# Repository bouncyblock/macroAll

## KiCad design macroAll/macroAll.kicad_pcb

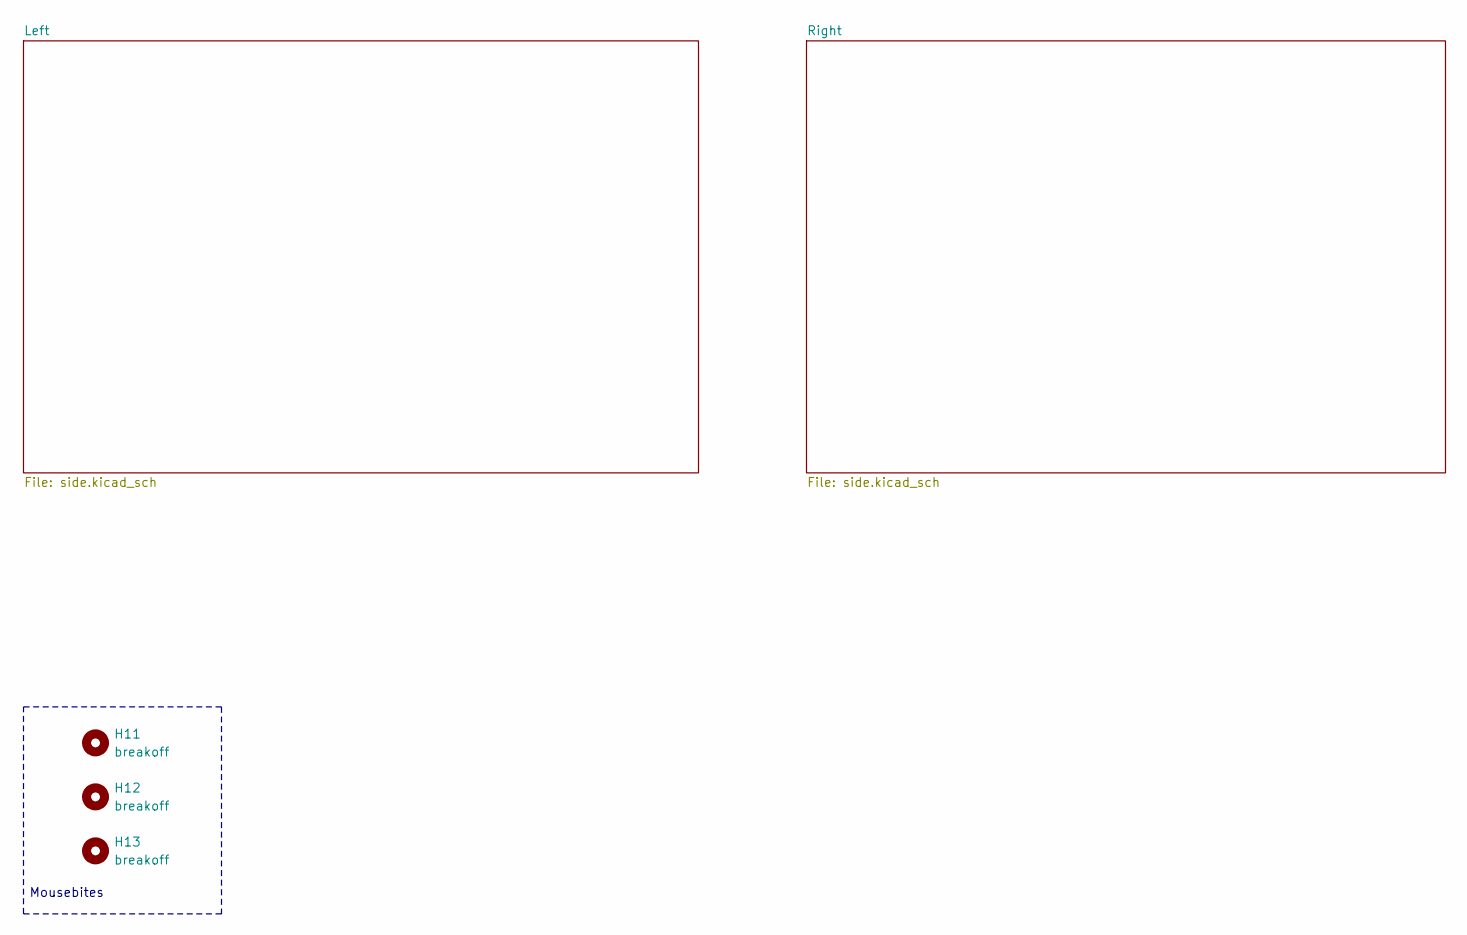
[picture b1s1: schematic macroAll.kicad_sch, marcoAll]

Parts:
H11, H12, H13: breakoff; mouse-bite-5mm-slot

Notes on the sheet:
Mousebites

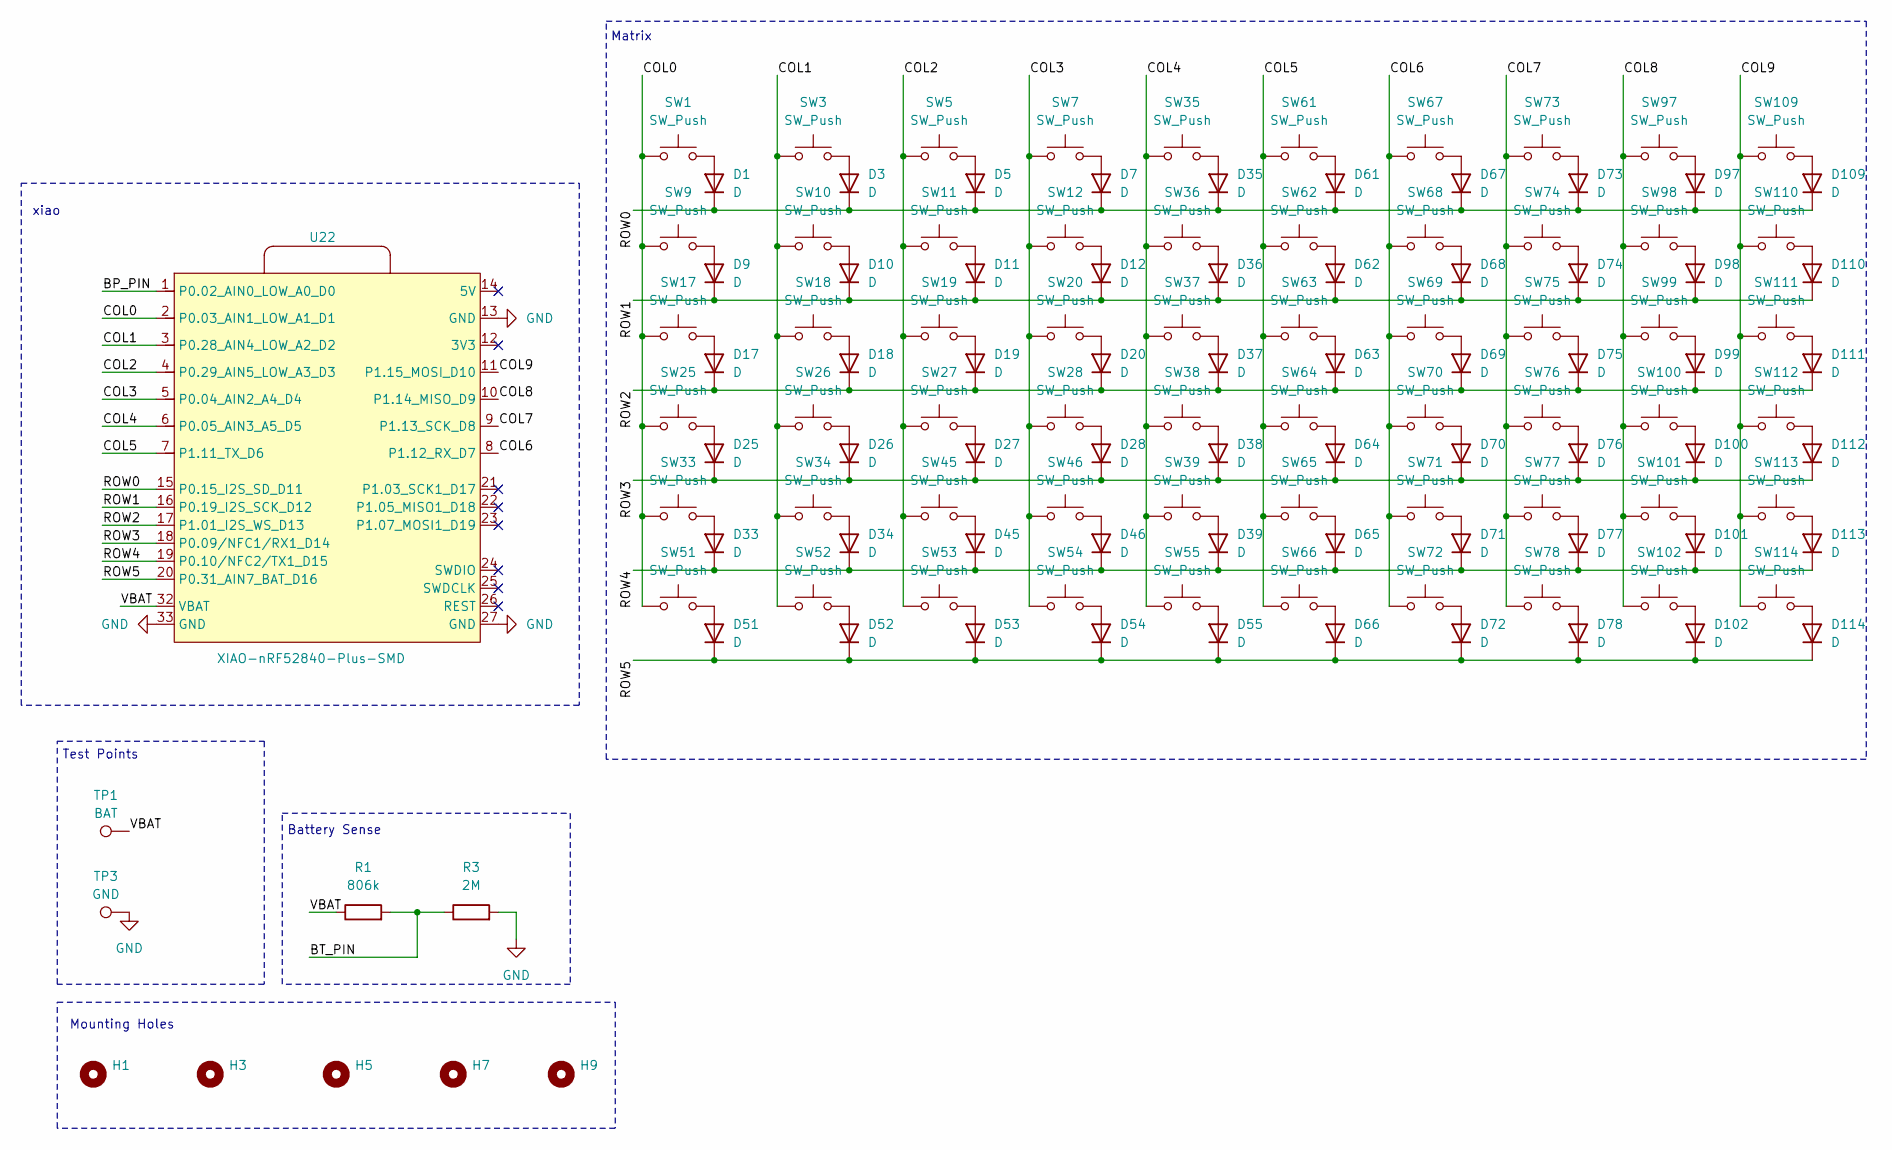
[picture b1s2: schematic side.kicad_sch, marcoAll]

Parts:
D1, D3, D5, D7, D9, D10, D11, D12, D17, D18, D19, D20, D25, D26, D27, D28, D33, D34, D35, D36, D37, D38, D39, D45, D46, D51, D52, D53, D54, D55, D61, D62, D63, D64, D65, D66, D67, D68, D69, D70, D71, D72, D73, D74, D75, D76, D77, D78, D97, D98, D99, D100, D101, D102, D109, D110, D111, D112, D113, D114: D; D_SOD-123
H1, H3, H5, H7, H9: MountingHole; MountingHole_2.5mm
R1: 806k; R_0805_2012Metric
R3: 2M; R_0805_2012Metric
SW1, SW3, SW5, SW7, SW9, SW10, SW11, SW12, SW17, SW18, SW19, SW20, SW25, SW26, SW27, SW28, SW33, SW34, SW35, SW36, SW37, SW38, SW39, SW45, SW46, SW51, SW52, SW53, SW54, SW55, SW61, SW62, SW63, SW64, SW65, SW66, SW67, SW68, SW69, SW70, SW71, SW72, SW73, SW74, SW75, SW76, SW77, SW78, SW97, SW98, SW99, SW100, SW101, SW102, SW109, SW110, SW111, SW112, SW113, SW114: SW_Push; SW_Hotswap_Kailh_Choc_V1
TP1: BAT; TestPoint_Pad_D2.0mm
TP3: GND; TestPoint_Pad_D2.0mm
U22: XIAO-nRF52840-Plus-SMD

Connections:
/Left/BP_PIN: U22.1 (P0.02_AIN0_LOW_A0_D0)
/Left/BT_PIN: R1.2, R3.1
/Left/COL0: SW1.1, SW9.1, SW17.1, SW25.1, SW33.1, SW51.1, U22.2 (P0.03_AIN1_LOW_A1_D1)
/Left/COL1: SW3.1, SW10.1, SW18.1, SW26.1, SW34.1, SW52.1, U22.3 (P0.28_AIN4_LOW_A2_D2)
/Left/COL2: SW5.1, SW11.1, SW19.1, SW27.1, SW45.1, SW53.1, U22.4 (P0.29_AIN5_LOW_A3_D3)
/Left/COL3: SW7.1, SW12.1, SW20.1, SW28.1, SW46.1, SW54.1, U22.5 (P0.04_AIN2_A4_D4)
/Left/COL4: SW35.1, SW36.1, SW37.1, SW38.1, SW39.1, SW55.1, U22.6 (P0.05_AIN3_A5_D5)
/Left/COL5: SW61.1, SW62.1, SW63.1, SW64.1, SW65.1, SW66.1, U22.7 (P1.11_TX_D6)
/Left/COL6: SW67.1, SW68.1, SW69.1, SW70.1, SW71.1, SW72.1, U22.8 (P1.12_RX_D7)
/Left/COL7: SW73.1, SW74.1, SW75.1, SW76.1, SW77.1, SW78.1, U22.9 (P1.13_SCK_D8)
/Left/COL8: SW97.1, SW98.1, SW99.1, SW100.1, SW101.1, SW102.1, U22.10 (P1.14_MISO_D9)
/Left/ROW0: D1.1 (K), D3.1 (K), D5.1 (K), D7.1 (K), D35.1 (K), D61.1 (K), D67.1 (K), D73.1 (K), D97.1 (K), D109.1 (K), U22.15 (P0.15_I2S_SD_D11)
/Left/ROW1: D9.1 (K), D10.1 (K), D11.1 (K), D12.1 (K), D36.1 (K), D62.1 (K), D68.1 (K), D74.1 (K), D98.1 (K), D110.1 (K), U22.16 (P0.19_I2S_SCK_D12)
/Left/ROW2: D17.1 (K), D18.1 (K), D19.1 (K), D20.1 (K), D37.1 (K), D63.1 (K), D69.1 (K), D75.1 (K), D99.1 (K), D111.1 (K), U22.17 (P1.01_I2S_WS_D13)
/Left/ROW4: D33.1 (K), D34.1 (K), D39.1 (K), D45.1 (K), D46.1 (K), D65.1 (K), D71.1 (K), D77.1 (K), D101.1 (K), D113.1 (K), U22.19 (P0.10/NFC2/TX1_D15)
/Left/VBAT: R1.1, TP1.1, U22.32 (VBAT)
GND: R3.2, TP3.1, U22.13 (GND), U22.27 (GND), U22.33 (GND); also elsewhere on the board
unnamed: D1.2 (A), SW1.2
unnamed: D3.2 (A), SW3.2
unnamed: D5.2 (A), SW5.2
unnamed: D7.2 (A), SW7.2
unnamed: D9.2 (A), SW9.2
unnamed: D10.2 (A), SW10.2
unnamed: D11.2 (A), SW11.2
unnamed: D12.2 (A), SW12.2
unnamed: D17.2 (A), SW17.2
unnamed: D18.2 (A), SW18.2
unnamed: D19.2 (A), SW19.2
unnamed: D20.2 (A), SW20.2
unnamed: D25.2 (A), SW25.2
unnamed: D26.2 (A), SW26.2
unnamed: D27.2 (A), SW27.2
unnamed: D28.2 (A), SW28.2
unnamed: D33.2 (A), SW33.2
unnamed: D34.2 (A), SW34.2
unnamed: D35.2 (A), SW35.2
unnamed: D36.2 (A), SW36.2
unnamed: D37.2 (A), SW37.2
unnamed: D38.2 (A), SW38.2
unnamed: D39.2 (A), SW39.2
unnamed: D45.2 (A), SW45.2
unnamed: D46.2 (A), SW46.2
unnamed: D51.2 (A), SW51.2
unnamed: D52.2 (A), SW52.2
unnamed: D53.2 (A), SW53.2
unnamed: D54.2 (A), SW54.2
unnamed: D55.2 (A), SW55.2
unnamed: D61.2 (A), SW61.2
unnamed: D62.2 (A), SW62.2
unnamed: D63.2 (A), SW63.2
unnamed: D64.2 (A), SW64.2
unnamed: D65.2 (A), SW65.2
unnamed: D66.2 (A), SW66.2
unnamed: D67.2 (A), SW67.2
unnamed: D68.2 (A), SW68.2
unnamed: D69.2 (A), SW69.2
unnamed: D70.2 (A), SW70.2
unnamed: D71.2 (A), SW71.2
unnamed: D72.2 (A), SW72.2
unnamed: D73.2 (A), SW73.2
unnamed: D74.2 (A), SW74.2
unnamed: D75.2 (A), SW75.2
unnamed: D76.2 (A), SW76.2
unnamed: D77.2 (A), SW77.2
unnamed: D78.2 (A), SW78.2
unnamed: D97.2 (A), SW97.2
unnamed: D98.2 (A), SW98.2
unnamed: D99.2 (A), SW99.2
unnamed: D100.2 (A), SW100.2
unnamed: D101.2 (A), SW101.2
unnamed: D102.2 (A), SW102.2
unnamed: D109.2 (A), SW109.2
unnamed: D110.2 (A), SW110.2
unnamed: D111.2 (A), SW111.2
unnamed: D113.2 (A), SW113.2

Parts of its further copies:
D2, D4, D6, D8, D13, D14, D15, D16, D21, D22, D23, D24, D29, D30, D31, D32, D40, D41, D42, D43, D44, D47, D48, D49, D50, D56, D57, D58, D59, D60, D79, D80, D81, D82, D83, D84, D85, D86, D87, D88, D89, D90, D91, D92, D93, D94, D95, D96, D103, D104, D105, D106, D107, D108, D115, D116, D117, D118, D119, D120: D; D_SOD-123
H2, H4, H6, H8, H10: MountingHole; MountingHole_2.5mm
R2: 806k; R_0805_2012Metric
R4: 2M; R_0805_2012Metric
SW2, SW4, SW6, SW8, SW13, SW14, SW15, SW16, SW21, SW22, SW23, SW24, SW29, SW30, SW31, SW32, SW40, SW41, SW42, SW43, SW44, SW47, SW48, SW49, SW50, SW56, SW57, SW58, SW59, SW60, SW79, SW80, SW81, SW82, SW83, SW84, SW85, SW86, SW87, SW88, SW89, SW90, SW91, SW92, SW93, SW94, SW95, SW96, SW103, SW104, SW105, SW106, SW107, SW108, SW115, SW116, SW117, SW118, SW119, SW120: SW_Push; SW_Hotswap_Kailh_Choc_V1
TP2: BAT; TestPoint_Pad_D2.0mm
TP4: GND; TestPoint_Pad_D2.0mm
U23: XIAO-nRF52840-Plus-SMD

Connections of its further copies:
/Right/BP_PIN: U23.1 (P0.02_AIN0_LOW_A0_D0)
/Right/BT_PIN: R2.2, R4.1
/Right/COL0: SW2.1, SW13.1, SW21.1, SW29.1, SW47.1, SW56.1, U23.2 (P0.03_AIN1_LOW_A1_D1)
/Right/COL1: SW4.1, SW14.1, SW22.1, SW30.1, SW48.1, SW57.1, U23.3 (P0.28_AIN4_LOW_A2_D2)
/Right/COL2: SW6.1, SW15.1, SW23.1, SW31.1, SW49.1, SW58.1, U23.4 (P0.29_AIN5_LOW_A3_D3)
/Right/COL3: SW8.1, SW16.1, SW24.1, SW32.1, SW50.1, SW59.1, U23.5 (P0.04_AIN2_A4_D4)
/Right/COL4: SW40.1, SW41.1, SW42.1, SW43.1, SW44.1, SW60.1, U23.6 (P0.05_AIN3_A5_D5)
/Right/COL5: SW79.1, SW80.1, SW81.1, SW82.1, SW83.1, SW84.1, U23.7 (P1.11_TX_D6)
/Right/COL6: SW85.1, SW86.1, SW87.1, SW88.1, SW89.1, SW90.1, U23.8 (P1.12_RX_D7)
/Right/COL7: SW91.1, SW92.1, SW93.1, SW94.1, SW95.1, SW96.1, U23.9 (P1.13_SCK_D8)
/Right/COL8: SW103.1, SW104.1, SW105.1, SW106.1, SW107.1, SW108.1, U23.10 (P1.14_MISO_D9)
/Right/ROW0: D2.1 (K), D4.1 (K), D6.1 (K), D8.1 (K), D40.1 (K), D79.1 (K), D85.1 (K), D91.1 (K), D103.1 (K), D115.1 (K), U23.15 (P0.15_I2S_SD_D11)
/Right/ROW1: D13.1 (K), D14.1 (K), D15.1 (K), D16.1 (K), D41.1 (K), D80.1 (K), D86.1 (K), D92.1 (K), D104.1 (K), D116.1 (K), U23.16 (P0.19_I2S_SCK_D12)
/Right/ROW2: D21.1 (K), D22.1 (K), D23.1 (K), D24.1 (K), D42.1 (K), D81.1 (K), D87.1 (K), D93.1 (K), D105.1 (K), D117.1 (K), U23.17 (P1.01_I2S_WS_D13)
/Right/ROW4: D44.1 (K), D47.1 (K), D48.1 (K), D49.1 (K), D50.1 (K), D83.1 (K), D89.1 (K), D95.1 (K), D107.1 (K), D119.1 (K), U23.19 (P0.10/NFC2/TX1_D15)
/Right/VBAT: R2.1, TP2.1, U23.32 (VBAT)
GND: R4.2, TP4.1, U23.13 (GND), U23.27 (GND), U23.33 (GND); also elsewhere on the board
unnamed: D2.2 (A), SW2.2
unnamed: D4.2 (A), SW4.2
unnamed: D6.2 (A), SW6.2
unnamed: D8.2 (A), SW8.2
unnamed: D13.2 (A), SW13.2
unnamed: D14.2 (A), SW14.2
unnamed: D15.2 (A), SW15.2
unnamed: D16.2 (A), SW16.2
unnamed: D21.2 (A), SW21.2
unnamed: D22.2 (A), SW22.2
unnamed: D23.2 (A), SW23.2
unnamed: D24.2 (A), SW24.2
unnamed: D29.2 (A), SW29.2
unnamed: D30.2 (A), SW30.2
unnamed: D31.2 (A), SW31.2
unnamed: D32.2 (A), SW32.2
unnamed: D40.2 (A), SW40.2
unnamed: D41.2 (A), SW41.2
unnamed: D42.2 (A), SW42.2
unnamed: D43.2 (A), SW43.2
unnamed: D44.2 (A), SW44.2
unnamed: D47.2 (A), SW47.2
unnamed: D48.2 (A), SW48.2
unnamed: D49.2 (A), SW49.2
unnamed: D50.2 (A), SW50.2
unnamed: D56.2 (A), SW56.2
unnamed: D57.2 (A), SW57.2
unnamed: D58.2 (A), SW58.2
unnamed: D59.2 (A), SW59.2
unnamed: D60.2 (A), SW60.2
unnamed: D79.2 (A), SW79.2
unnamed: D80.2 (A), SW80.2
unnamed: D81.2 (A), SW81.2
unnamed: D82.2 (A), SW82.2
unnamed: D83.2 (A), SW83.2
unnamed: D84.2 (A), SW84.2
unnamed: D85.2 (A), SW85.2
unnamed: D86.2 (A), SW86.2
unnamed: D87.2 (A), SW87.2
unnamed: D88.2 (A), SW88.2
unnamed: D89.2 (A), SW89.2
unnamed: D90.2 (A), SW90.2
unnamed: D91.2 (A), SW91.2
unnamed: D92.2 (A), SW92.2
unnamed: D93.2 (A), SW93.2
unnamed: D94.2 (A), SW94.2
unnamed: D95.2 (A), SW95.2
unnamed: D96.2 (A), SW96.2
unnamed: D103.2 (A), SW103.2
unnamed: D104.2 (A), SW104.2
unnamed: D105.2 (A), SW105.2
unnamed: D106.2 (A), SW106.2
unnamed: D107.2 (A), SW107.2
unnamed: D108.2 (A), SW108.2
unnamed: D115.2 (A), SW115.2
unnamed: D116.2 (A), SW116.2
unnamed: D117.2 (A), SW117.2
unnamed: D118.2 (A), SW118.2
unnamed: D119.2 (A), SW119.2
unnamed: D120.2 (A), SW120.2

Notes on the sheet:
Matrix
xiao
Mounting Holes
Battery Sense
Test Points

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
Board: 2 copper layers, 259 parts (0 on the bottom side), 155 nets, no tracks yet.

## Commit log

2025-10-29 added readme
2025-10-30 added OPL libraries and KiCad init
2025-10-30 added remaining libraries and set up sheets
2025-10-31 added circuitry
2025-11-04 Changed circuit board used
2025-11-05 fixed footprint
2025-11-07 half of half keyboard layout finished
2025-11-08 left side placement
2025-11-09 placed left components, redid left edgecut design, led placement
